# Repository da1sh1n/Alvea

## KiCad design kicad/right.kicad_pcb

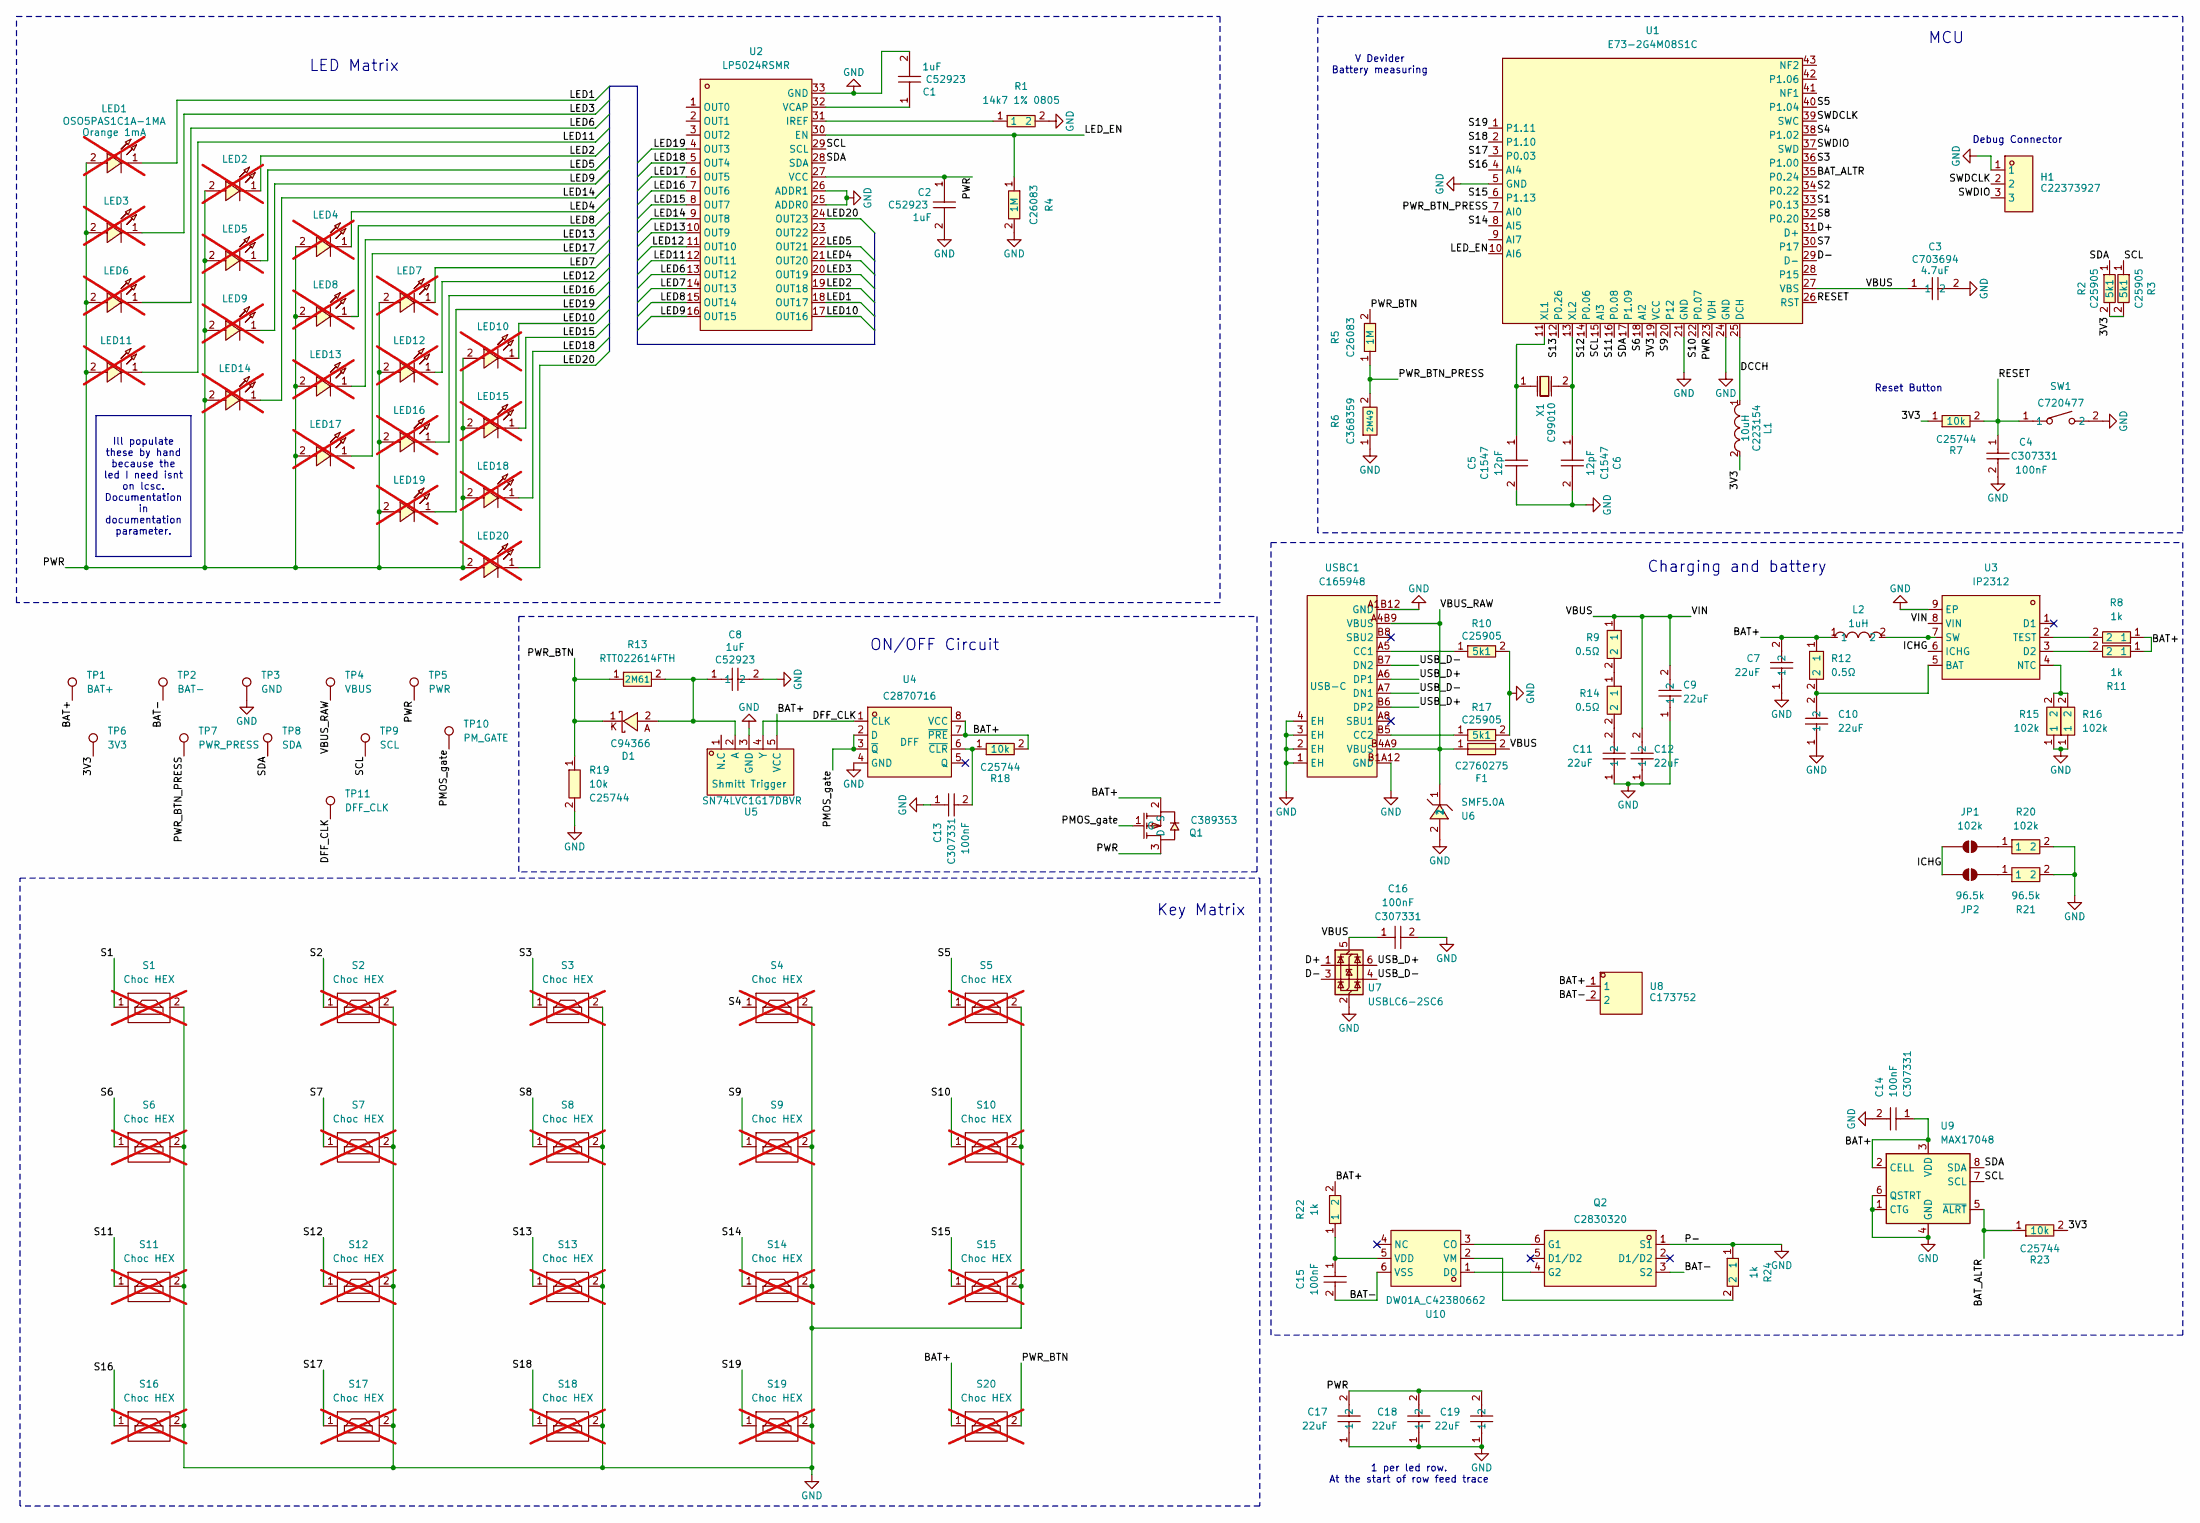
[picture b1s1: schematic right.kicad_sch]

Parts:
C1, C2, C8: CL05A105KA5NQNC; C0402; LCSC Part C52923
C3: ZRB15XR61A475KE01D; C0402; MPN ZRB15XR61A475KE01D; LCSC Part C703694
C4, C13, C14, C15, C16: CL05B104KB54PNC; C0402; LCSC Part C307331
C5, C6: 0402CG120J500NT; C0402; LCSC Part C1547
C7, C9, C10, C11, C12, C17, C18, C19: 22uF; C0805; MPN CL21A226KOQNNNE; LCSC Part C296720
D1: NSR05F20NXT5G; DSN2_L1.0-W0.6-RD; LCSC Part C94366
F1: SMD1206-150C-16V; F1206; LCSC Part C2760275
H1: HC-PM254-8.5H-1X3PW; HDR-TH_3P-P2.54_HC-PM254-8.5H-1X3PW; LCSC Part C22373927
JP1: 102k; SolderJumper-2_P1.3mm_Open_TrianglePad1.0x1.5mm
JP2: 96.5k; SolderJumper-2_P1.3mm_Open_TrianglePad1.0x1.5mm
L1: BRC2016T100K; IND-SMD_L2.0-W1.6_BRC2016; LCSC Part C223154
L2: 1uH; IND-SMD_L2.5-W2.0; MPN TMS252012ALM-1R0MTAA; LCSC Part C1882521
LED1, LED2, LED3, LED4, LED5, LED6, LED7, LED8, LED9, LED10, LED11, LED12, LED13, LED14, LED15, LED16, LED17, LED18, LED19, LED20: OSO5PAS1C1A-1MA; LED-SMD_L3.2-W2.8-LS3.5-RD-BLUE; LCSC Part OSO5PAS1C1A-1MA -> on tme.ue; not fitted
Q1: PMF170XP,115; SOT-323-3_L2.0-W1.3-P1.30-LS2.1-BR; LCSC Part C389353
Q2: FS8205A_C2830320; SOT-23-6_L2.9-W1.6-P0.95-LS2.8-BR; LCSC Part C2830320
R1: 14k7 1% 0805; R0805; MPN 0805W8F1472T5E; LCSC Part C17458
R2, R3, R10, R17: 0402WGF5101TCE; R0402; LCSC Part C25905
R4, R5: 0402WGF1004TCE; R0402; LCSC Part C26083
R6: WR04W2494FTL; R0402; LCSC Part C368359
R7, R18, R19, R23: 0402WGF1002TCE; R0402; LCSC Part C25744
R8, R11, R22, R24: 1k; R0402; MPN 0402WGF1001TCE; LCSC Part C11702
R9, R12, R14: 0.5Ω; R0402; MPN 0402WGF500LTCE; LCSC Part C423160
R13: RTT022614FTH; R0402; MPN RTT022614FTH; LCSC Part C166493
R15, R16, R20: 102k; R0402; MPN RT0402BRD07102KL; LCSC Part C852473
R21: 96.5k; R0402; MPN RT0402BRD0796K5L; LCSC Part C852962
S1, S2, S3, S4, S5, S6, S7, S8, S9, S10, S11, S12, S13, S14, S15, S16, S17, S18, S19, S20: Choc HEX; PG1350_hotswap_reversed; not fitted
SW1: TS-1088-AR02016; SW-SMD_L3.9-W3.0-P4.45; LCSC Part C720477
TP1: BAT+; TestPoint_Pad_D2.0mm
TP2: BAT-; TestPoint_Pad_D2.0mm
TP3: GND; TestPoint_Pad_D2.0mm
TP4: VBUS; TestPoint_Pad_D2.0mm
TP5: PWR; TestPoint_Pad_D2.0mm
TP6: 3V3; TestPoint_Pad_D2.0mm
TP7: PWR_PRESS; TestPoint_Pad_D2.0mm
TP8: SDA; TestPoint_Pad_D2.0mm
TP9: SCL; TestPoint_Pad_D2.0mm
TP10: PM_GATE; TestPoint_Pad_D2.0mm
TP11: DFF_CLK; TestPoint_Pad_D2.0mm
U1: E73-2G4M08S1C; WIRELM-SMD_E73-2G4M08S1C; LCSC Part C356849
U2: LP5024RSMR; VQFN-32_L4.0-W4.0-P0.40-TL-EP; LCSC Part C427525
U3: IP2312; SOP-8_L4.9-W3.9-P1.27-LS6.0-BL-EP; MPN IP2312U_VSET; LCSC Part C605432
U4: SN74LVC1G74DQER; X2SON-8_L1.4-W1.0-P0.35-BL; LCSC Part C2870716
U5: SN74LVC1G17DBVR; SOT-23-5_L3.0-W1.7-P0.95-LS2.8-BR; MPN SN74LVC1G17DBVR; LCSC Part C7836
U6: SMF5.0A; SOD-123FL_L2.8-W1.8-LS3.6-RD; MPN SMF5.0A; LCSC Part C2990427
U7: USBLC6-2SC6; SOT-23-6; LCSC Part C7519
U8: S2B-PH-K-S(LF)(SN); CONN-TH_S2B-PH-K-S-LF-SN; LCSC Part C173752
U9: MAX17048; DFN-8_2x2mm_P0.5mm_EP1.2x0.8mm; LCSC Part C2682616
U10: DW01A_C42380662; SOT-23-6_L2.9-W1.6-P0.95-LS2.9-BL; LCSC Part C42380662
USBC1: TYPE-C-31-M-12; USB-C_SMD-TYPE-C-31-M-12_1; LCSC Part C165948
X1: FC-13532.768KHZ9PF20PPM; OSC-SMD_L3.2-W1.5; LCSC Part C99010

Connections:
/3V3: L1.2, R2.2, R3.2, R7.1, R23.2, TP6.1 (1_1), U1.19 (VCC)
/BAT+: C7.2, C14.1, L2.1, Q1.2 (S), R8.1, R11.1, R12.1, R18.2, R22.2, S20.1, TP1.1 (1_1), U4.7 (~PRE), U4.8 (VCC), U5.5 (VCC), U8.1, U9.2 (CELL), U9.3 (VDD)
/BAT-: C15.2, Q2.3 (S2), TP2.1 (1_1), U8.2, U10.6 (VSS)
/BAT_ALTR: R23.1, U1.35 (P0.24), U9.5 (~ALRT)
/D+: U1.31 (D+), U7.1 (I/O1)
/D-: U1.29 (D-), U7.3 (I/O2)
/DCCH: L1.1, U1.25 (DCH)
/DFF_CLK: TP11.1 (1_1), U4.1 (CLK), U5.4 (Y)
/ICHG: JP1.1 (A), JP2.1 (A), U3.6 (ICHG)
/LED1: LED1.1, U2.18 (OUT17)
/LED2: LED2.1, U2.19 (OUT18)
/LED3: LED3.1, U2.20 (OUT19)
/LED4: LED4.1, U2.21 (OUT20)
/LED5: LED5.1, U2.22 (OUT21)
/LED6: LED6.1, U2.13 (OUT12)
/LED7: LED7.1, U2.14 (OUT13)
/LED8: LED8.1, U2.15 (OUT14)
/LED9: LED9.1, U2.16 (OUT15)
/LED10: LED10.1, U2.17 (OUT16)
/LED11: LED11.1, U2.12 (OUT11)
/LED12: LED12.1, U2.11 (OUT10)
/LED13: LED13.1, U2.10 (OUT9)
/LED14: LED14.1, U2.9 (OUT8)
/LED15: LED15.1, U2.8 (OUT7)
/LED16: LED16.1, U2.7 (OUT6)
/LED17: LED17.1, U2.6 (OUT5)
/LED18: LED18.1, U2.5 (OUT4)
/LED19: LED19.1, U2.4 (OUT3)
/LED20: LED20.1, U2.24 (OUT23)
/LED_EN: R4.1, U1.10 (AI6), U2.30 (EN)
/PMOS_gate: Q1.1 (G), TP10.1 (1_1), U4.2 (D), U4.3 (~Q)
/PWR: C2.1, C17.2, C18.2, C19.2, LED1.2, LED2.2, LED3.2, LED4.2, LED5.2, LED6.2, LED7.2, LED8.2, LED9.2, LED10.2, LED11.2, LED12.2, LED13.2, LED14.2, LED15.2, LED16.2, LED17.2, LED18.2, LED19.2, LED20.2, Q1.3 (D), TP5.1 (1_1), U1.23 (VDH), U2.27 (VCC)
/PWR_BTN: D1.1, R5.2, R13.1, R19.1, S20.2
/PWR_BTN_PRESS: R5.1, R6.2, TP7.1 (1_1), U1.7 (AI0)
/RESET: C4.1, R7.2, SW1.1, U1.26 (RST)
/S1: S1.1, U1.33 (P0.13)
/S2: S2.1, U1.34 (P0.22)
/S3: S3.1, U1.36 (P1.00)
/S4: S4.1, U1.38 (P1.02)
/S5: S5.1, U1.40 (P1.04)
/S6: S6.1, U1.18 (AI2)
/S7: S7.1, U1.30 (P17)
/S8: S8.1, U1.32 (P0.20)
/S9: S9.1, U1.20 (P12)
/S10: S10.1, U1.22 (P0.07)
/S11: S11.1, U1.16 (P0.08)
/S12: S12.1, U1.14 (P0.06)
/S13: S13.1, U1.12 (P0.26)
/S14: S14.1, U1.8 (AI5)
/S15: S15.1, U1.6 (P1.13)
/S16: S16.1, U1.4 (AI4)
/S17: S17.1, U1.3 (P0.03)
/S18: S18.1, U1.2 (P1.10)
/S19: S19.1, U1.1 (P1.11)
/SCL: R3.1, TP9.1 (1_1), U1.15 (AI3), U2.29 (SCL), U9.7 (SCL)
/SDA: R2.1, TP8.1 (1_1), U1.17 (P1.09), U2.28 (SDA), U9.8 (SDA)
/SWDCLK: H1.2, U1.39 (SWC)
/SWDIO: H1.3, U1.37 (SWD)
/USB_D+: U7.6 (I/O1), USBC1.A6 (DP1), USBC1.B6 (DP2)
/USB_D-: U7.4 (I/O2), USBC1.A7 (DN1), USBC1.B7 (DN2)
/VBUS: C3.1, C9.2, C12.2, C16.1, F1.2, R9.1, U1.27 (VBS), U3.8 (VIN), U7.5 (VBUS)
/VBUS_RAW: F1.1, TP4.1 (1_1), U6.1, USBC1.A4B9 (VBUS), USBC1.B4A9 (VBUS)
GND: C1.2, C2.2, C3.2, C4.2, C5.2, C6.2, C7.1, C8.2, C9.1, C10.1, C11.1, C12.1, C13.1, C14.2, C16.2, C17.1, C18.1, C19.1, H1.1, Q2.1 (S1), R1.2, R4.2, R6.1, R10.2, R15.1, R16.1, R17.2, R19.2, R20.2, R21.2, R24.1, S1.2, S2.2, S3.2, S4.2, S5.2, S6.2, S7.2, S8.2, S9.2, S10.2, S11.2, S12.2, S13.2, S14.2, S15.2, S16.2, S17.2, S18.2, S19.2, SW1.2, TP3.1 (1_1), U1.5 (GND), U1.21 (GND), U1.24 (GND), U2.25 (ADDR0), U2.26 (ADDR1), U2.33 (GND), U3.9 (EP), U4.4 (GND), U5.3 (GND), U6.2, U7.2 (GND), U9.1 (CTG), U9.4 (GND), U9.6 (QSTRT), U9.9 (GND), USBC1.1 (EH), USBC1.2 (EH), USBC1.3 (EH), USBC1.4 (EH), USBC1.A1B12 (GND), USBC1.B1A12 (GND)
unnamed: C11.2, R14.2
unnamed: JP1.2 (B), R20.1
unnamed: JP2.2 (B), R21.1
unnamed: Q2.6 (G1), U10.3 (CO)
unnamed: Q2.4 (G2), U10.1 (DO)
unnamed: R9.2, R14.1
unnamed: C5.1, U1.11 (XL1), X1.1
unnamed: C6.1, U1.13 (XL2), X1.2
unnamed: R1.1, U2.31 (IREF)
unnamed: C1.1, U2.32 (VCAP)
unnamed: C10.2, R12.2, U3.5 (BAT)
unnamed: R11.2, U3.3 (D2)
unnamed: R15.2, R16.2, U3.4 (NTC)
unnamed: L2.2, U3.7 (SW)
unnamed: R8.2, U3.2 (TEST)
unnamed: C13.2, R18.1, U4.6 (~CLR)
unnamed: C8.1, D1.2, R13.2, U5.2 (A)
unnamed: C15.1, R22.1, U10.5 (VDD)
unnamed: R24.2, U10.2 (VM)
unnamed: R10.1, USBC1.A5 (CC1)
unnamed: R17.1, USBC1.B5 (CC2)

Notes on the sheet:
Charging and battery
MCU
Debug Connector
ON/OFF Circuit
Reset Button
Key Matrix
V Devider Battery measuring
LED Matrix
1 per led row. At the start of row feed trace
Ill populate these by hand because the led I need isnt on lcsc. Documentation in documentation parameter.

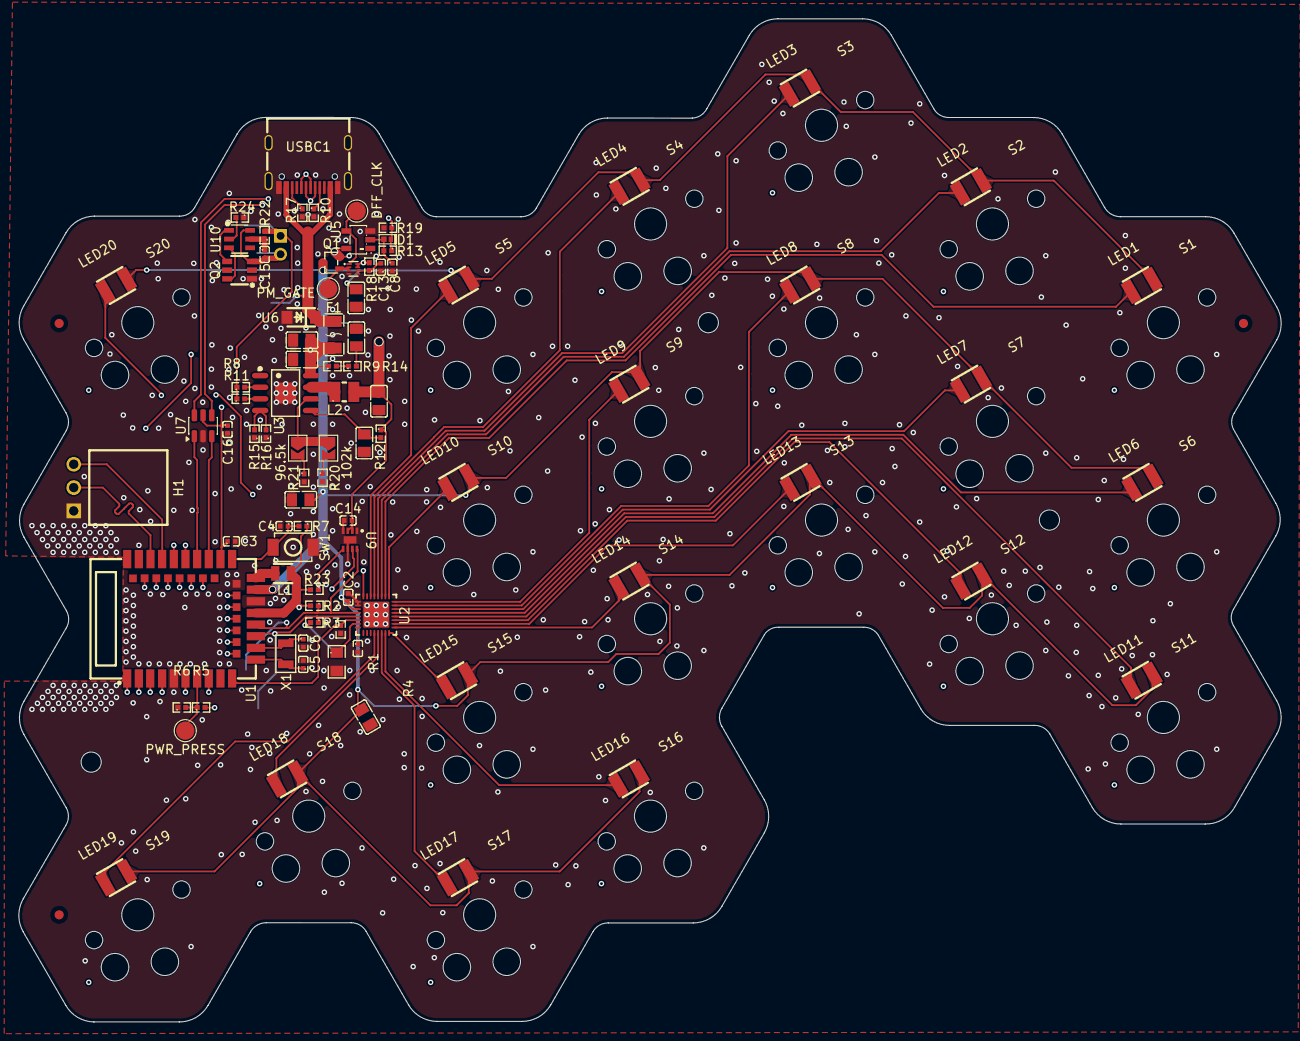
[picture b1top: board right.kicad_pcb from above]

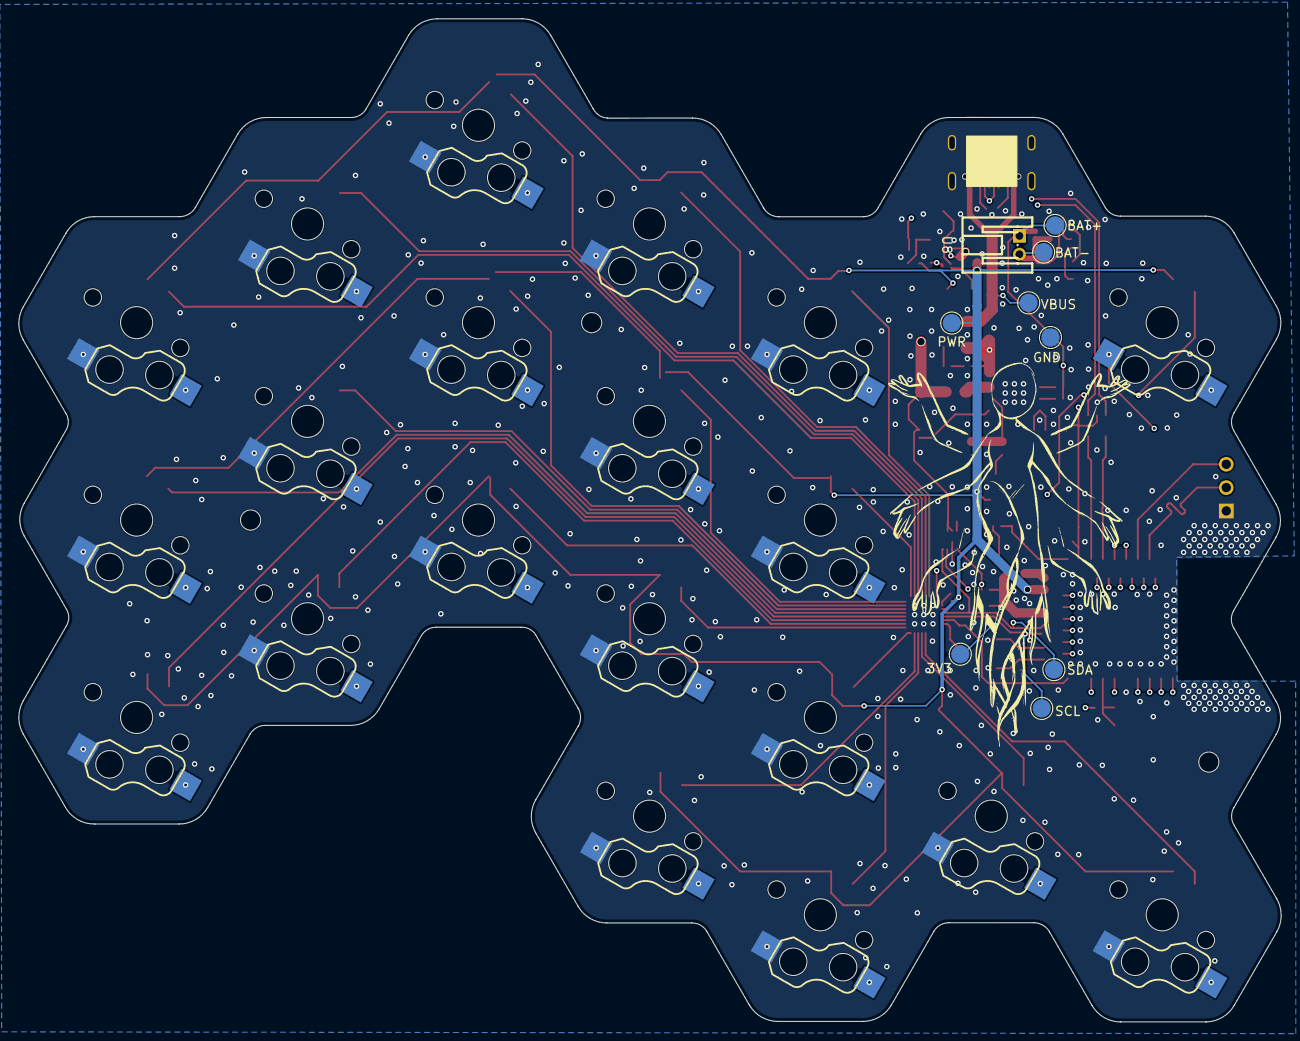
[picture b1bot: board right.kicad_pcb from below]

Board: 4 copper layers, 137.5 x 109.3 mm, 120 parts (30 on the bottom side), 84 nets.

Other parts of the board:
Fi4, Fi5: Fiducial_1mm_Mask2mm
Fi6: Fiducial_1mm_Mask2mm
G**: LOGO; handy

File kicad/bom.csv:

"Reference","Qty","Value","DNP","Exclude from BOM","Exclude from Board","Footprint","Datasheet","LCSC Part"
"C1,C2,C8","3","CL05A105KA5NQNC","","","","easyeda2kicad:C0402","https://lcsc.com/datasheet/C52923.pdf","C52923"
"C3","1","ZRB15XR61A475KE01D","","","","easyeda2kicad:C0402","https://lcsc.com/product-detail/Multilayer-Ceramic-Capacitor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","C703694"
"C4,C13,C14,C15,C16","5","CL05B104KB54PNC","","","","easyeda2kicad:C0402","https://lcsc.com/datasheet/C307331.pdf","C307331"
"C5,C6","2","0402CG120J500NT","","","","easyeda2kicad:C0402","https://lcsc.com/datasheet/C1547.pdf","C1547"
"C7,C9,C10,C11,C12,C17,C18,C19","8","22uF","","","","easyeda2kicad:C0805","https://lcsc.com/product-detail/Others_Samsung-Electro-Mecha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","C296720"
"D1","1","NSR05F20NXT5G","","","","easyeda2kicad:DSN2_L1.0-W0.6-RD","https://lcsc.com/product-detail/Schottky-Barrier-Diodes-SBD_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","C94366"
"F1","1","SMD1206-150C-16V","","","","easyeda2kicad:F1206","","C2760275"
"H1","1","HC-PM254-8.5H-1X3PW","","","",":HDR-TH_3P-P2.54_HC-PM254-8.5H-1X3PW","","C22373927"
"L1","1","BRC2016T100K","","","",":IND-SMD_L2.0-W1.6_BRC2016","https://lcsc.com/product-detail/New-Arrivals_Taiyo-Yuden-BRC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","C223154"
"L2","1","1uH","","","","easyeda2kicad:IND-SMD_L2.5-W2.0","https://www.lcsc.com/datasheet/C1882521.pdf","C1882521"
"Q1","1","PMF170XP,115","","","","easyeda2kicad:SOT-323-3_L2.0-W1.3-P1.30-LS2.1-BR","https://lcsc.com/product-detail/MOSFET_Nexperia-PMF170XP-115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","C389353"
"Q2","1","FS8205A_C2830320","","","","easyeda2kicad:SOT-23-6_L2.9-W1.6-P0.95-LS2.8-BR","","C2830320"
"R1","1","14k7 1% 0805","","","","easyeda2kicad:R0805","https://lcsc.com/product-detail/Chip-Resistor-Surface-Mount-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","C17458"
"R2,R3,R10,R17","4","0402WGF5101TCE","","","","easyeda2kicad:R0402","https://lcsc.com/datasheet/C25905.pdf","C25905"
"R4,R5","2","0402WGF1004TCE","","","","easyeda2kicad:R0402","https://lcsc.com/datasheet/C26083.pdf","C26083"
"R6","1","WR04W2494FTL","","","","easyeda2kicad:R0402","https://lcsc.com/product-detail/Others_Walsin-Tech-Corp-WR04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","C368359"
"R7,R18,R19,R23","4","0402WGF1002TCE","","","","easyeda2kicad:R0402","https://lcsc.com/datasheet/C25744.pdf","C25744"
"R8,R11,R22,R24","4","1k","","","","easyeda2kicad:R0402","https://lcsc.com/product-detail/Chip-Resistor-Surface-Mount-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","C11702"
"R9,R12,R14","3","0.5Ω","","","","easyeda2kicad:R0402","https://lcsc.com/product-detail/Chip-Resistor-Surface-Mount_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","C423160"
"R13","1","RTT022614FTH","","","","easyeda2kicad:R0402","https://lcsc.com/datasheet/C166493.pdf","C166493"
"R15,R16,R20","3","102k","","","","easyeda2kicad:R0402","https://www.lcsc.com/datasheet/C852473.pdf","C852473"
"R21","1","96.5k","","","","easyeda2kicad:R0402","https://www.lcsc.com/datasheet/C852962.pdf","C852962"
"SW1","1","TS-1088-AR02016","","","","easyeda2kicad:SW-SMD_L3.9-W3.0-P4.45","https://lcsc.com/product-detail/Tactile-Switches_XUNPU-TS-10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","C720477"
"U1","1","E73-2G4M08S1C","","","",":WIRELM-SMD_E73-2G4M08S1C","https://lcsc.com/product-detail/_Chengdu-Ebyte-Elec-Tech-E73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","C356849"
"U2","1","LP5024RSMR","","","",":VQFN-32_L4.0-W4.0-P0.40-TL-EP","","C427525"
"U3","1","IP2312","","","","easyeda2kicad:SOP-8_L4.9-W3.9-P1.27-LS6.0-BL-EP","https://lcsc.com/product-detail/DC-DC-Converters_INJOINIC-IP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","C605432"
"U4","1","SN74LVC1G74DQER","","","",":X2SON-8_L1.4-W1.0-P0.35-BL","","C2870716"
"U5","1","SN74LVC1G17DBVR","","","","easyeda2kicad:SOT-23-5_L3.0-W1.7-P0.95-LS2.8-BR","https://www.lcsc.com/datasheet/C7836.pdf","C7836"
"U6","1","SMF5.0A","","","","easyeda2kicad:SOD-123FL_L2.8-W1.8-LS3.6-RD","https://www.lcsc.com/datasheet/C2990427.pdf","C2990427"
"U7","1","USBLC6-2SC6","","","","Package_TO_SOT_SMD:SOT-23-6","https://www.st.com/resource/en/datasheet/usblc6-2.pdf","C7519"
"U8","1","S2B-PH-K-S(LF)(SN)","","","",":CONN-TH_S2B-PH-K-S-LF-SN","https://lcsc.com/product-detail/PH-Connectors_JST-Sales-Amer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","C173752"
"U9","1","MAX17048","","","","PCM_SparkFun-Semiconductor-Standard:DFN-8_2x2mm_P0.5mm_EP1.2x0.8mm","https://www.analog.com/media/en/technical-documentation/data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","C2682616"
"U10","1","DW01A_C42380662","","","",":SOT-23-6_L2.9-W1.6-P0.95-LS2.9-BL","","C42380662"
"USBC1","1","TYPE-C-31-M-12","","","","easyeda2kicad:USB-C_SMD-TYPE-C-31-M-12_1","https://lcsc.com/product-detail/USB-Type-C_Korean-Hroparts-E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","C165948"
"X1","1","FC-13532.768KHZ9PF20PPM","","","","easyeda2kicad:OSC-SMD_L3.2-W1.5","https://lcsc.com/product-detail/SMD-Crystals_EPSON_FC-13532-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","C99010"

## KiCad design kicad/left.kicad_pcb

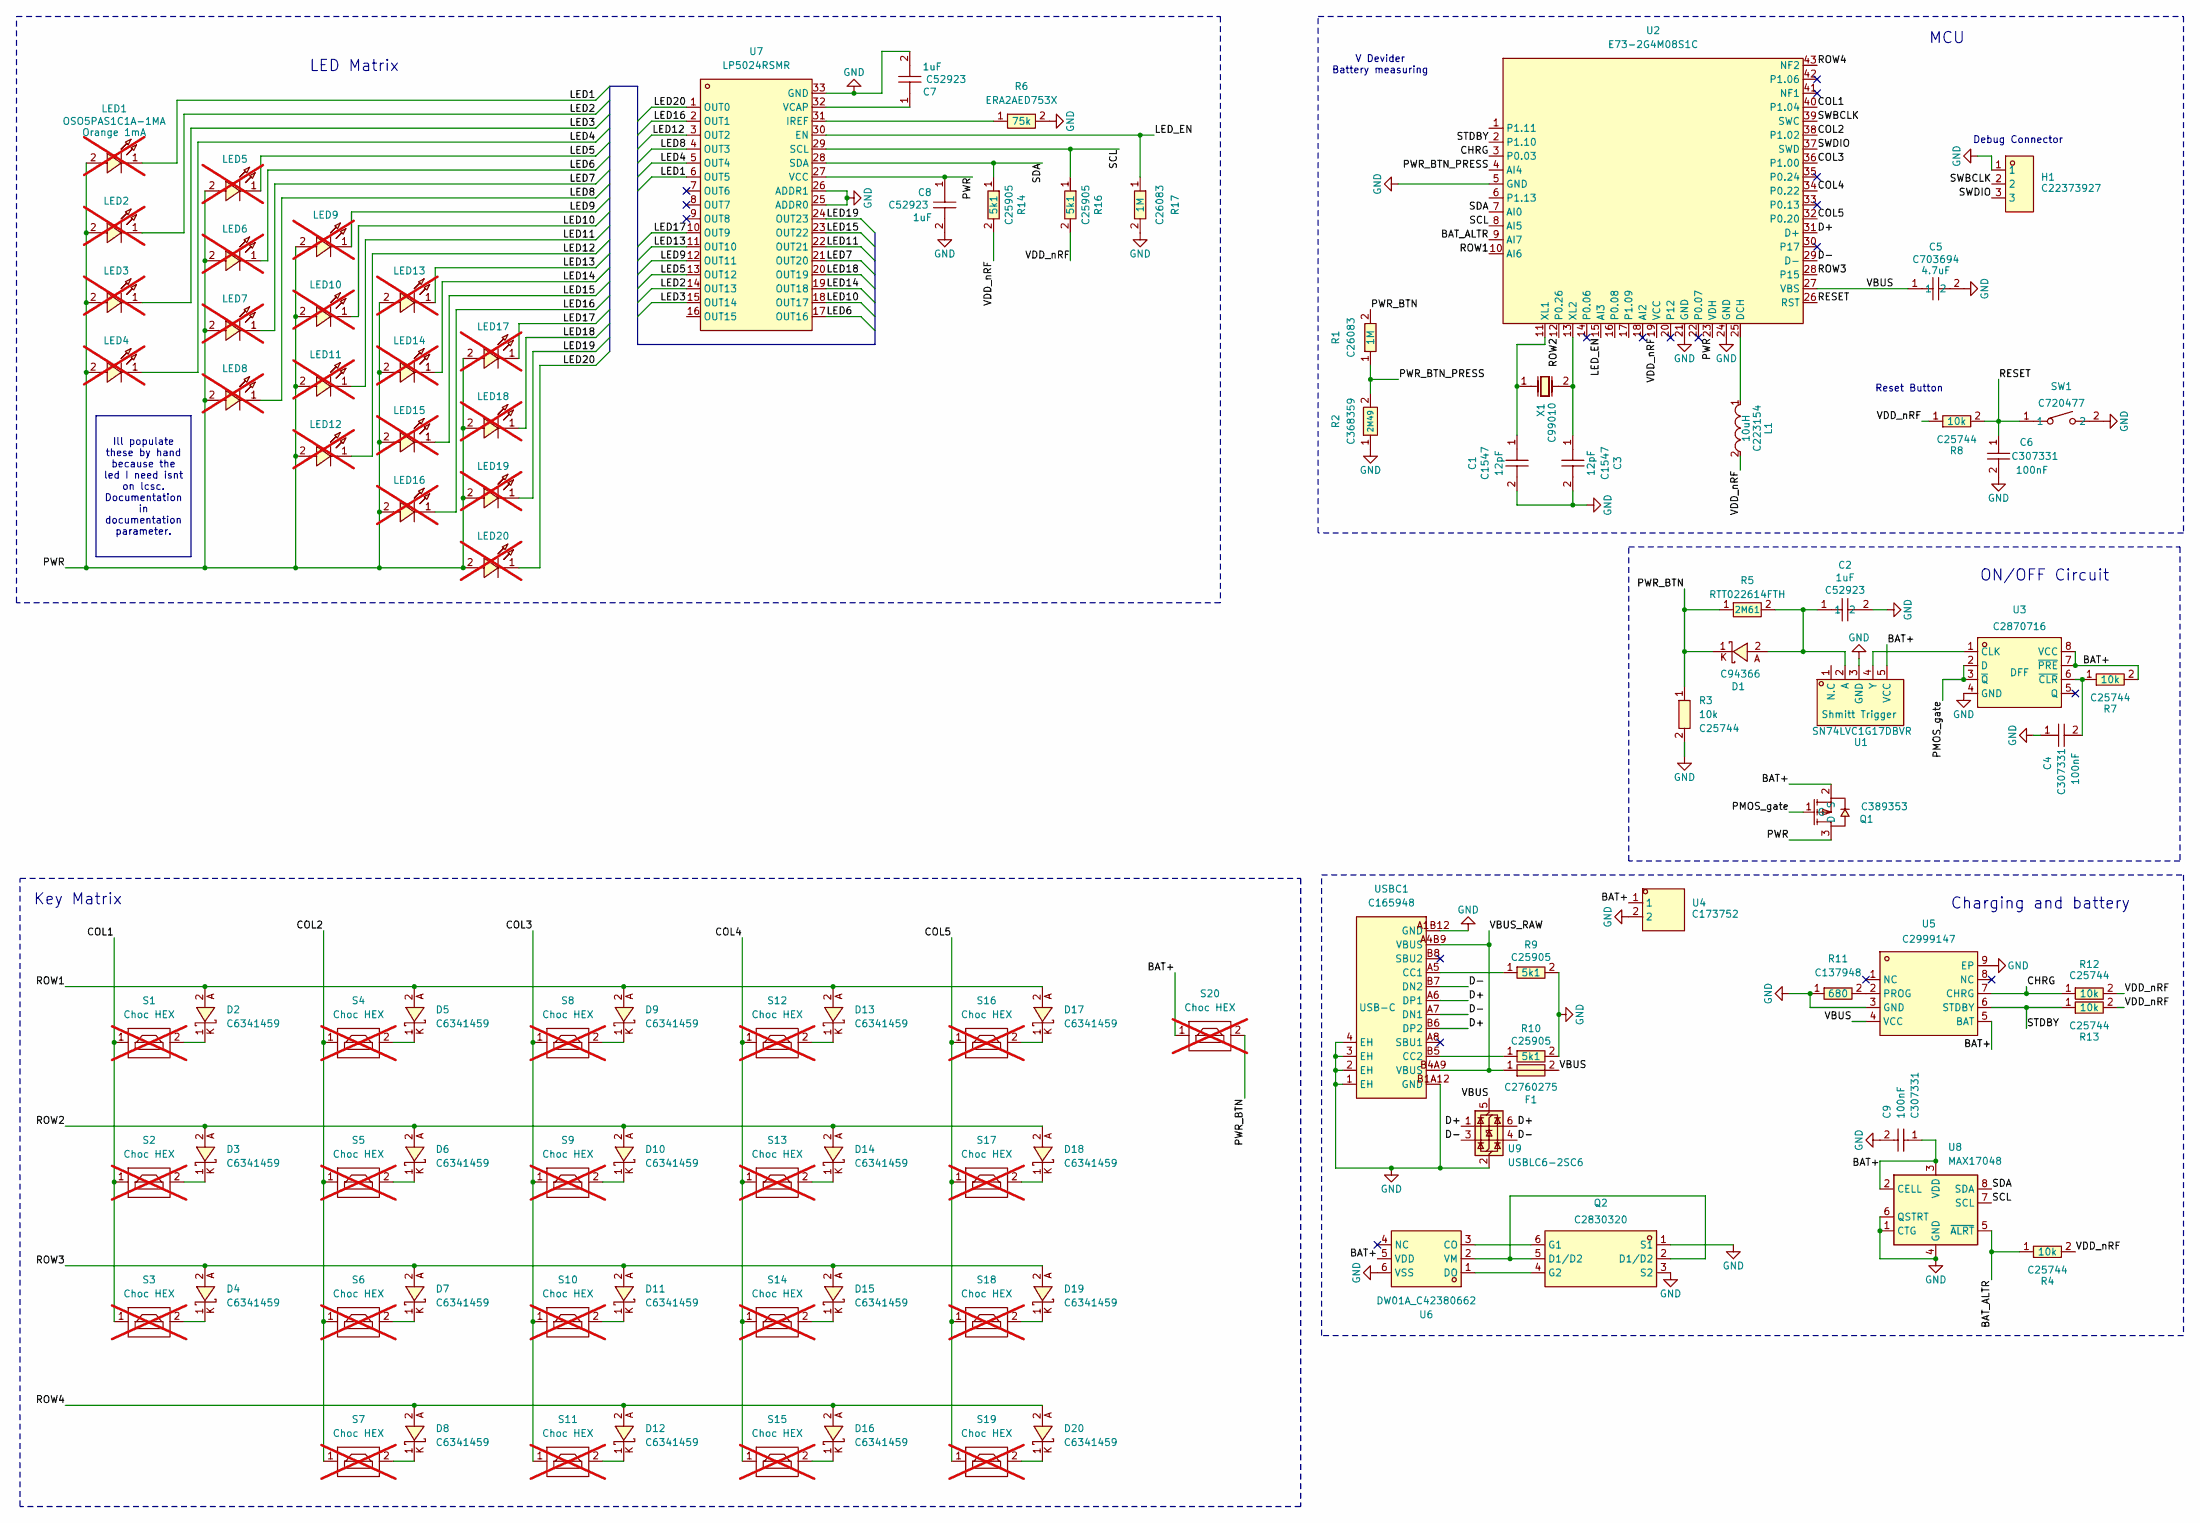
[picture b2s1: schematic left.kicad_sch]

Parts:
C1, C3: 0402CG120J500NT; C0402; LCSC Part C1547
C2, C7, C8: CL05A105KA5NQNC; C0402; LCSC Part C52923
C4, C6, C9: CL05B104KB54PNC; C0402; LCSC Part C307331
C5: ZRB15XR61A475KE01D; C0402; MPN ZRB15XR61A475KE01D; LCSC Part C703694
D1: NSR05F20NXT5G; DSN2_L1.0-W0.6-RD; LCSC Part C94366
D2, D3, D4, D5, D6, D7, D8, D9, D10, D11, D12, D13, D14, D15, D16, D17, D18, D19, D20: CDSQC4148-HF; X1-DFN1006-2_L1.0-W0.6-RD; LCSC Part C6341459
F1: SMD1206-150C-16V; F1206; LCSC Part C2760275
H1: HC-PM254-8.5H-1X3PW; HDR-TH_3P-P2.54_HC-PM254-8.5H-1X3PW; LCSC Part C22373927
L1: BRC2016T100K; IND-SMD_L2.0-W1.6_BRC2016; LCSC Part C223154
LED1, LED2, LED3, LED4, LED5, LED6, LED7, LED8, LED9, LED10, LED11, LED12, LED13, LED14, LED15, LED16, LED17, LED18, LED19, LED20: OSO5PAS1C1A-1MA; LED-SMD_L3.2-W2.8-LS3.5-RD-BLUE; LCSC Part OSO5PAS1C1A-1MA -> on tme.ue; not fitted
Q1: PMF170XP,115; SOT-323-3_L2.0-W1.3-P1.30-LS2.1-BR; LCSC Part C389353
Q2: FS8205A_C2830320; SOT-23-6_L2.9-W1.6-P0.95-LS2.8-BR; LCSC Part C2830320
R1, R17: 0402WGF1004TCE; R0402; LCSC Part C26083
R2: WR04W2494FTL; R0402; LCSC Part C368359
R3, R4, R7, R8, R12, R13: 0402WGF1002TCE; R0402; LCSC Part C25744
R5: RTT022614FTH; R0402; MPN RTT022614FTH; LCSC Part C166493
R6: ERA2AED753X; R0402; MPN ERA2AED753X; LCSC Part C491105
R9, R10, R14, R16: 0402WGF5101TCE; R0402; LCSC Part C25905
R11: RC0402FR-07680RL; R0402; LCSC Part C137948
S1, S2, S3, S4, S5, S6, S7, S8, S9, S10, S11, S12, S13, S14, S15, S16, S17, S18, S19, S20: Choc HEX; PG1350_hotswap_reversed; not fitted
SW1: TS-1088-AR02016; SW-SMD_L3.9-W3.0-P4.45; LCSC Part C720477
U1: SN74LVC1G17DBVR; SOT-23-5_L3.0-W1.7-P0.95-LS2.8-BR; MPN SN74LVC1G17DBVR; LCSC Part C7836
U2: E73-2G4M08S1C; WIRELM-SMD_E73-2G4M08S1C; LCSC Part C356849
U3: SN74LVC1G74DQER; X2SON-8_L1.4-W1.0-P0.35-BL; LCSC Part C2870716
U4: S2B-PH-K-S(LF)(SN); CONN-TH_S2B-PH-K-S-LF-SN; LCSC Part C173752
U5: BL8573CS8TR; ESOP-8_L4.9-W3.9-P1.27-LS6.0-BL-EP; LCSC Part C2999147
U6: DW01A_C42380662; SOT-23-6_L2.9-W1.6-P0.95-LS2.9-BL; LCSC Part C42380662
U7: LP5024RSMR; VQFN-32_L4.0-W4.0-P0.40-TL-EP; LCSC Part C427525
U8: MAX17048; DFN-8_2x2mm_P0.5mm_EP1.2x0.8mm; LCSC Part C2682616
U9: USBLC6-2SC6; SOT-23-6; LCSC Part C7519
USBC1: TYPE-C-31-M-12; USB-C_SMD-TYPE-C-31-M-12_1; LCSC Part C165948
X1: FC-13532.768KHZ9PF20PPM; OSC-SMD_L3.2-W1.5; LCSC Part C99010

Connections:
/BAT+: C9.1, Q1.2 (S), R7.2, S20.1, U1.5 (VCC), U3.7 (~PRE), U3.8 (VCC), U4.1, U5.5 (BAT), U6.5 (VDD), U8.2 (CELL), U8.3 (VDD); also elsewhere on the board
/BAT_ALTR: R4.1, U2.9 (AI7), U8.5 (~ALRT)
/CHRG: R12.1, U2.3 (P0.03), U5.7 (CHRG)
/COL1: S1.1, S2.1, S3.1, U2.40 (P1.04)
/COL2: S4.1, S5.1, S6.1, S7.1, U2.38 (P1.02)
/COL3: S8.1, S9.1, S10.1, S11.1, U2.36 (P1.00)
/COL4: S12.1, S13.1, S14.1, S15.1, U2.34 (P0.22)
/COL5: S16.1, S17.1, S18.1, S19.1, U2.32 (P0.20)
/D+: U2.31 (D+), U9.1 (I/O1), U9.6 (I/O1), USBC1.A6 (DP1), USBC1.B6 (DP2)
/D-: U2.29 (D-), U9.3 (I/O2), U9.4 (I/O2), USBC1.A7 (DN1), USBC1.B7 (DN2)
/LED1: LED1.1, U7.6 (OUT5)
/LED2: LED2.1, U7.14 (OUT13)
/LED3: LED3.1, U7.15 (OUT14)
/LED4: LED4.1, U7.5 (OUT4)
/LED5: LED5.1, U7.13 (OUT12)
/LED6: LED6.1, U7.17 (OUT16)
/LED7: LED7.1, U7.21 (OUT20)
/LED8: LED8.1, U7.4 (OUT3)
/LED9: LED9.1, U7.12 (OUT11)
/LED10: LED10.1, U7.18 (OUT17)
/LED11: LED11.1, U7.22 (OUT21)
/LED12: LED12.1, U7.3 (OUT2)
/LED13: LED13.1, U7.11 (OUT10)
/LED14: LED14.1, U7.19 (OUT18)
/LED15: LED15.1, U7.23 (OUT22)
/LED16: LED16.1, U7.2 (OUT1)
/LED17: LED17.1, U7.10 (OUT9)
/LED18: LED18.1, U7.20 (OUT19)
/LED19: LED19.1, U7.24 (OUT23)
/LED20: LED20.1, U7.1 (OUT0)
/LED_EN: R17.1, U2.15 (AI3), U7.30 (EN)
/PMOS_gate: Q1.1 (G), U3.2 (D), U3.3 (~Q)
/PWR: C8.1, LED1.2, LED2.2, LED3.2, LED4.2, LED5.2, LED6.2, LED7.2, LED8.2, LED9.2, LED10.2, LED11.2, LED12.2, LED13.2, LED14.2, LED15.2, LED16.2, LED17.2, LED18.2, LED19.2, LED20.2, Q1.3 (D), U2.23 (VDH), U7.27 (VCC); also elsewhere on the board
/PWR_BTN: D1.1, R1.2, R3.1, R5.1, S20.2
/PWR_BTN_PRESS: R1.1, R2.2, U2.4 (AI4)
/RESET: C6.1, R8.2, SW1.1, U2.26 (RST)
/ROW1: D2.2, D5.2, D9.2, D13.2, D17.2, U2.10 (AI6)
/ROW2: D3.2, D6.2, D10.2, D14.2, D18.2, U2.12 (P0.26)
/ROW3: D4.2, D7.2, D11.2, D15.2, D19.2, U2.28 (P15)
/ROW4: D8.2, D12.2, D16.2, D20.2, U2.43 (NF2)
/SCL: R16.1, U2.8 (AI5), U7.29 (SCL), U8.7 (SCL)
/SDA: R14.1, U2.7 (AI0), U7.28 (SDA), U8.8 (SDA)
/STDBY: R13.1, U2.2 (P1.10), U5.6 (STDBY)
/SWBCLK: H1.2, U2.39 (SWC)
/SWDIO: H1.3, U2.37 (SWD)
/VBUS: C5.1, F1.2, U2.27 (VBS), U5.4 (VCC), U9.5 (VBUS); also elsewhere on the board
/VBUS_RAW: F1.1, USBC1.A4B9 (VBUS), USBC1.B4A9 (VBUS)
/VDD_nRF: L1.2, R4.2, R8.1, R12.2, R13.2, R14.2, R16.2, U2.19 (VCC); also elsewhere on the board
GND: C1.2, C2.2, C3.2, C4.1, C5.2, C6.2, C7.2, C8.2, C9.2, H1.1, Q2.1 (S1), Q2.3 (S2), R2.1, R3.2, R6.2, R9.2, R10.2, R11.1, R17.2, SW1.2, U1.3 (GND), U2.5 (GND), U2.21 (GND), U2.24 (GND), U3.4 (GND), U4.2, U5.3 (GND), U5.9 (EP), U6.6 (VSS), U7.25 (ADDR0), U7.26 (ADDR1), U7.33 (GND), U8.1 (CTG), U8.4 (GND), U8.6 (QSTRT), U8.9 (GND), U9.2 (GND), USBC1.1 (EH), USBC1.2 (EH), USBC1.3 (EH), USBC1.4 (EH), USBC1.A1B12 (GND), USBC1.B1A12 (GND); also elsewhere on the board
unnamed: D2.1, S1.2
unnamed: D3.1, S2.2
unnamed: D4.1, S3.2
unnamed: D5.1, S4.2
unnamed: D6.1, S5.2
unnamed: D7.1, S6.2
unnamed: D8.1, S7.2
unnamed: D9.1, S8.2
unnamed: D10.1, S9.2
unnamed: D11.1, S10.2
unnamed: D12.1, S11.2
unnamed: D13.1, S12.2
unnamed: D14.1, S13.2
unnamed: D15.1, S14.2
unnamed: D16.1, S15.2
unnamed: D17.1, S16.2
unnamed: D18.1, S17.2
unnamed: D19.1, S18.2
unnamed: D20.1, S19.2
unnamed: Q2.6 (G1), U6.3 (CO)
unnamed: Q2.4 (G2), U6.1 (DO)
unnamed: C2.1, D1.2, R5.2, U1.2 (A)
unnamed: U1.4 (Y), U3.1 (CLK)
unnamed: L1.1, U2.25 (DCH)
unnamed: C1.1, U2.11 (XL1), X1.1
unnamed: C3.1, U2.13 (XL2), X1.2
unnamed: C4.2, R7.1, U3.6 (~CLR)
unnamed: R11.2, U5.2 (PROG)
unnamed: Q2.2 (D1/D2), Q2.5 (D1/D2), U6.2 (VM)
unnamed: R6.1, U7.31 (IREF)
unnamed: C7.1, U7.32 (VCAP)
unnamed: R9.1, USBC1.A5 (CC1)
unnamed: R10.1, USBC1.B5 (CC2)

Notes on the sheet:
Debug Connector
Reset Button
MCU
LED Matrix
Charging and battery
ON/OFF Circuit
Key Matrix
V Devider Battery measuring
Ill populate these by hand because the led I need isnt on lcsc. Documentation in documentation parameter.
